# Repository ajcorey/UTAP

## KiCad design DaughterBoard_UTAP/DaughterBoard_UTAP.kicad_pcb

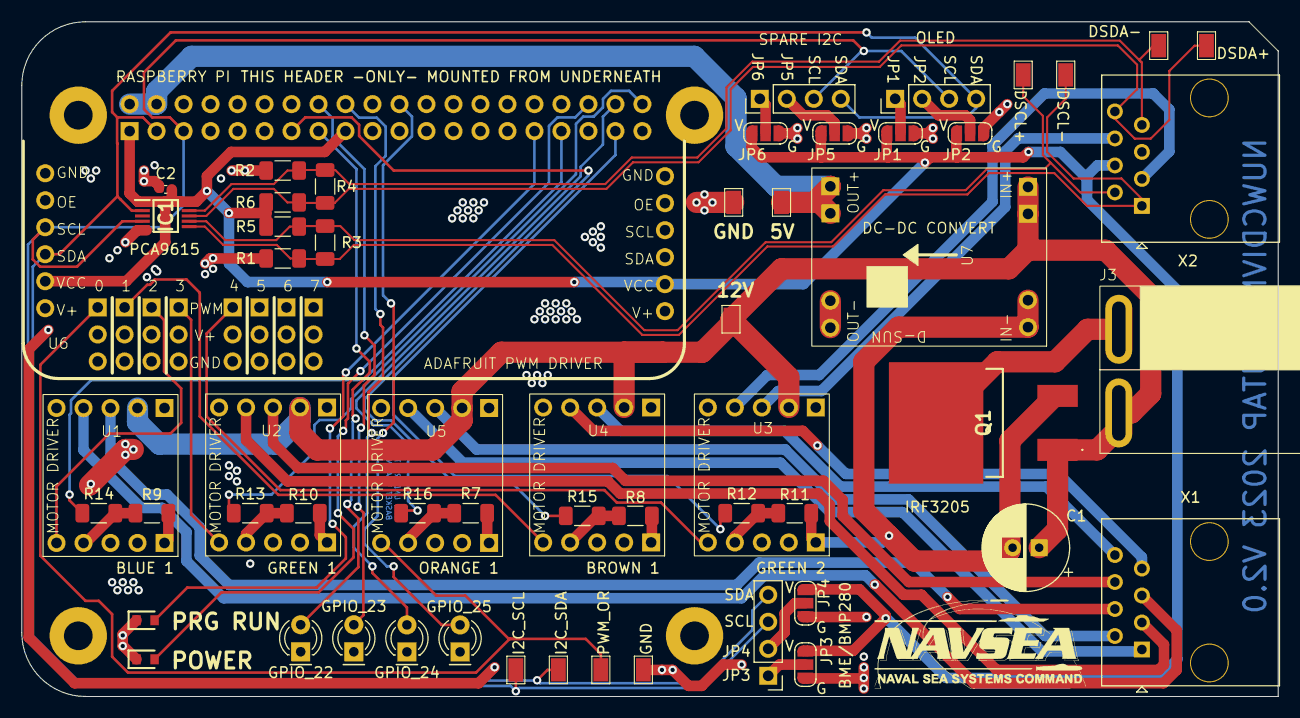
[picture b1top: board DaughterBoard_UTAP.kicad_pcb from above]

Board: 2 copper layers, 118.2 x 63.5 mm, 57 parts (1 on the bottom side), 48 nets.

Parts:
    X1    ,     X2    : RJ45; RJ45_OST_PJ012-8P8CX_Vertical
BME/BMP280: BME/BMP280; PinHeader_1x04_P2.54mm_Vertical
C1: 865080657018; CP_Radial_D8.0mm_P2.50mm
C2: 1.0uF; C_0402_1005Metric_Pad0.74x0.62mm_HandSolder
GND: S2751-46R; S275146R
GPIO_22, GPIO_23, GPIO_24, GPIO_25: LED; LED_D3.0mm
IC1: PCA9615DPZ; SOP50P490X110-10N
J1: Conn_01x04_Socket; PinHeader_1x04_P2.54mm_Vertical
J3: Screw_Terminal_01x02; AndersonPowerPole
J4: Raspberry_Pi_2_3; PinSocket_2x20_P2.54mm_Vertical
JP1, JP2, JP3, JP4, JP5, JP6: SolderJumper_3_Open; SolderJumper-3_P1.3mm_Open_RoundedPad1.0x1.5mm_NumberLabels
LED1, LED2: APHM1608VRBXF_A-5MAV; LEDC1608X45N
OLED: OLED; PinHeader_1x04_P2.54mm_Vertical
Q1: IRF3205STRLPBF
R1, R2, R5, R6: 390; R_1206_3216Metric_Pad1.30x1.75mm_HandSolder
R3, R4, R12, R13, R14, R15, R16: 100; R_1206_3216Metric_Pad1.30x1.75mm_HandSolder
R7, R8, R9, R10, R11: 10K; R_1206_3216Metric_Pad1.30x1.75mm_HandSolder
TP1, TP2, TP3, TP4, TP5, TP6, TP7, TP8, TP9, TP10: S2751-46R; S275146R
U1, U2, U3, U4, U5: MAX14870Breakout
U6: PCA9685; PWM_DRIVER_TRUNCATE
U7: DCDC_CONVERT

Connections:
+3.3V: X2.4, C2.1, IC1.1 (VDD(A)), IC1.10 (VDD(B)), J4.1 (3V3), J4.17 (3V3), JP1.1 (A), JP2.1 (A), JP3.1 (A), JP4.1 (A), JP5.1 (A), JP6.1 (A), R5.1, R6.1, U6.5 (VCC)
+5V: J4.2 (5V), J4.4 (5V), TP10.1, U7.4 (OUT+)
+12V: C1.1 (+), J3.2, Q1.1 (G), TP9.1, U1.7 (VIN), U2.7 (VIN), U3.7 (VIN), U4.7 (VIN), U5.7 (VIN), U7.3 (IN+)
-BATT: J3.1, Q1.2 (D)
/BLU_MOTOR: X1.4, U1.8 (M2)
/BLU_STR_MOTOR: X1.5, U1.9 (M1)
/BRO_MOTOR: X1.8, U4.8 (M2)
/BRO_STR_MOTOR: X1.7, U4.9 (M1)
/DSCL+: X2.2, IC1.7 (DSCLP), R3.1, R5.2, TP6.1
/DSCL-: X2.1, IC1.6 (DSCLM), R1.1, R3.2, TP5.1
/DSDA+: X2.8, IC1.8 (DSDAP), R4.1, R6.2, TP3.1
/DSDA-: X2.7, IC1.9 (DSDAM), R2.1, R4.2, TP4.1
/GPIO_13: J4.33 (PWM1/GPIO13), R14.1
/GPIO_20: J4.38 (GPIO20/MOSI1), R16.1
/GPIO_21: J4.40 (GPIO21/SCLK1), R13.1
/GPIO_22: GPIO_22.2 (A), J4.15 (GPIO22)
/GPIO_23: GPIO_23.2 (A), J4.16 (GPIO23)
/GPIO_24: GPIO_24.2 (A), J4.18 (GPIO24)
/GPIO_25: GPIO_25.2 (A), J4.22 (GPIO25)
/GPIO_26: J4.37 (GPIO26), R12.1
/GPIO_27: J4.13 (GPIO27), R15.1
/GRE_1_MOTOR: X1.6, U2.8 (M2)
/GRE_2_MOTOR: X2.6, U3.8 (M2)
/GRE_STR_1_MOTOR: X1.3, U2.9 (M1)
/GRE_STR_2_MOTOR: X2.3, U3.9 (M1)
/I2C1_SCL: BME/BMP280.3 (SCL), IC1.4 (SCL), J1.3, J4.5 (SCL/GPIO3), OLED.3 (SCL), TP1.1, U6.3 (SCL)
/I2C1_SDA: BME/BMP280.4 (SDA), IC1.2 (SDA), J1.4, J4.3 (SDA/GPIO2), OLED.4 (SDA), TP2.1, U6.4 (SDA)
/OR_MOTOR: X1.2, U5.8 (M2)
/OR_STR_MOTOR: X1.1, U5.9 (M1)
/PWM1_OR: TP7.1, U5.1 (PWM), U6.7 (PWM0)
/PWM2_BRO: U4.1 (PWM), U6.10 (PWM1)
/PWM3_BLU: U1.1 (PWM), U6.13 (PWM2)
/PWM4_GRE_1: U2.1 (PWM), U6.16 (PWM3)
/PWM5_GRE_2: U3.1 (PWM), U6.19 (GND4)
GND: X2.5, C1.2 (-), C2.2, GND.1, GPIO_22.1 (K), GPIO_23.1 (K), GPIO_24.1 (K), GPIO_25.1 (K), IC1.5 (VSS), J4.6 (GND), J4.9 (GND), J4.14 (GND), J4.20 (GND), J4.25 (GND), J4.30 (GND), J4.34 (GND), J4.39 (GND), JP1.3 (B), JP2.3 (B), JP3.3 (B), JP4.3 (B), JP5.3 (B), JP6.3 (B), LED1.1 (K), LED2.1 (K), Q1.3 (S), R1.2, R2.2, R7.1, R8.1, R9.1, R10.1, R11.1, TP8.1, U1.5 (GND), U1.6 (GND), U2.5 (GND), U2.6 (GND), U3.5 (GND), U3.6 (GND), U4.5 (GND), U4.6 (GND), U5.5 (GND), U5.6 (GND), U6.1 (GND), U7.1 (OUT-), U7.2 (IN-)
unnamed: J1.1, JP6.2 (C)
unnamed: J1.2, JP5.2 (C)
unnamed: J4.31 (GCLK2/GPIO6), LED1.2 (A)
unnamed: J4.36 (GPIO16), LED2.2 (A)
unnamed: JP1.2 (C), OLED.1
unnamed: JP2.2 (C), OLED.2
unnamed: BME/BMP280.1 (P3), JP3.2 (C)
unnamed: BME/BMP280.2 (P4), JP4.2 (C)
unnamed: R9.2, R14.2, U1.2 (DIR)
unnamed: R10.2, R13.2, U2.2 (DIR)
unnamed: R11.2, R12.2, U3.2 (DIR)
unnamed: R8.2, R15.2, U4.2 (DIR)
unnamed: R7.2, R16.2, U5.2 (DIR)

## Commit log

2023-10-03 initial commit with the complete but non-printed board
